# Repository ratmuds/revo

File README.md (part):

# revo

a cool robot arm

# Demo Video
# 

# What is it?

revo is a robot arm I made that is 6 DoF, and is equipped with 12 PCBs (5 unique designs), multiple cameras, many microcontrollers, and a lot of files

# Why?

I wanted to make a robot arm that punched above its weight. The price is pretty similar to smaller robot arms on Amazon that may not include cameras, which would need to be purchased separately. The way this is achieved is by using cheap servos, servos that are 100% NOT made for this purpose, and adding most of the functionality of a smart servo back by using a TON of PCBs. It was a lot of soldering. I just wanted to make something that had more features for less money :)

### Motors

Each motor has voltage, current, and a connector for a NTC thermistor for temperature monitoring. The MG996R servos each have a sensor PCB that plugs in and provides angle data via an AS5600 IC and another IC for a magnetic endstop since I had issues with physical endstops before. The MG996R needs a custom case to mount everything, which took me an incredible amount of time to get working due to super weird tolerances, especially the way I have it working requiring a separate 3D printed extension for the shaft to mount a magnet. The code also has to track this magnet super fast and track how many full revolutions it makes, and calculates the correct real angle from that. It's also running LADRC instead of basic sweep or PID, which has helped a little with jittering and general inaccuracies.

Each MG996R servo has two JST-VH connectors and two JST-1.25mm connectors. They daisy chain 6V and a RS-485 bus for reliable data transfer. The daisy chaining helps with the wiring, and the differential signals help with noise resistance and the distance. Each servo compares a checksum and magic byte that is received to verify data integrity before loading it into structs and using the data. They have multiple LEDs to provide information such as errors, calibration status, data corruption, invalid PCB ID, code alive status, etc.

### Mainboard

The mainboard has a RPi Pico for controlling, and a bunch of sensors for the DS5180 servo motors. The mainboard also has a two step power circuit that requires a logic signal from the Pico and the E-STOP to be depressed to allow the electricity to flow through. This is then routed to 3 separate buck modules that regulate the voltage. There is a 6V module for the MG996Rs, and two 7.4V modules for the DS5180s. There are also two smaller modules for 12V and 3.3V.

### Control

There are multiple ways to control the robot arm, such as manually controlling the values in the dashboard, dragging IK in the dashboard, or the coolest way, VR. You can see it in action in the demo video above :)

## Some images

### More images in the [`/PCB`](PCB/) folder!

# Looking back

There are a lot of not great things with this arm. The mainboard is incredibly hard to assemble. The screws like to fall out. There are cables everywhere despite me trying to clean it up a bit. And it's inaccurate. But that's because the motors I'm using are literally like $5 each. I would recommend better motors if you want to make a robot arm, but this project was just to see if I could do it and pushing my limits in all fields like programming, electronics, and CAD/mechanical design.

# "Installation"

## Please do not replicate this robot arm.
It is a proof of concept that is not ready for real world use. There are no instructions for building it because of that reason. It is a fragile piece of robotics and not meant for any sort of practical usage or replication! If you really want to, it's not that difficult though if you look through the CAD :)

There is a lot of different files.

 - `firmware/dashboard`: The dashboard for controlling and viewing telemetry data. Use `pnpm i` to install, `pnpm run dev` to run.
 - `firmware/mainboard-firmware`: Please use the Arduino IDE and compile for your RPi Pico board.
 - `firmware/pc-code`: Python backend for telemetry and cameras. Install dependencies with `pip install -r requirements.txt` (or use `uv run`). Run `python camera_server.py` to host the cameras (loads three) and `python main.py` to host the communication layer between the mainboard and the web dashboard.
 - `firmware/servo-firmware`: Please use PlatformIO in VSCode (or similar) and compile. You will need a UPDI programmer to upload the code to the MG996Rs containing ATtiny3216s. Note that the servos cannot output any serial so you will have to rely on LEDs if it's not communicating with the mainboard!

## VR

I used a Meta Quest 2 and used the Link app on my PC (GPU required) and you can go to `localhost:5173/VR` while hosting the dashboard to access the WebXR page.

## PCBs

The five PCB designs are in the `/PCB` folder. There are more images in that folder for reference. I ordered them and hand soldered them, which took a long time but I got faster as time went on.

## Bill of Materials (this is so so so long)

### Hardware & Components

Please don't actually build this project, but if you do ORDER SPARES!!!!!!

| Name | Type | Amount | Link | Notes |
| --- | --- | --- | --- | --- |
| 80KG High Torque Digital Servo (270°) | Servo Motor | 3 | [AliExpress](https://www.aliexpress.com/item/1005007314488392.html) | 1/5 scale waterproof metal gear servos for base, shoulder, and elbow joints |
| MG996R Metal Gear Digital Servo | Servo Motor | 4 | [AliExpress](https://www.aliexpress.com/item/1005008413371371.html) | 4.8V–6.0V high torque standard servos for wrist and gripper joints |
| 18T Round Disc Metal Servo Horn | Hardware | 2 | [AliExpress](https://www.aliexpress.us/item/3256807206931134.html?spm=a2g0o.productlist.main.9.741d8cce7npNM8&algo_pvid=76ea85b5-3475-48e7-a43c-c0fa06abfd4f&algo_exp_id=76ea85b5-3475-48e7-a43c-c0fa06abfd4f-8&pdp_ext_f=%7B%22order%22%3A%2287%22%2C%22eval%22%3A%221%22%2C%22fromPage%22%3A%22search%22%7D&pdp_npi=6%40dis%21USD%213.12%213.12%21%21%213.12%213.12%21%402101e75417906272356213761e0f7f%2112000040563545569%21sea%21US%212891746612%21X%211%210%21n_tag%3A-29919%3Bd%3A6dcb8e0a%3Bm03_new_user%3A-29895&curPageLogUid=LFs17y7q5TM3&utparam-url=scene%3Asearch%7Cquery_from%3A%7Cx_object_id%3A1005007393245886%7C_p_origin_prod%3A) | Round disc steering servo horn for 60KG/80KG/150KG servos |
| MG996R Metal Servo Horns (25T) | Hardware | 4 | [AliExpress](https://www.aliexpress.us/item/3256811964799543.html?spm=a2g0o.productlist.main.9.7dd94603On9EAE&algo_pvid=e16d6fb9-ca4b-46d7-a97f-2976e7b034ed&algo_exp_id=e16d6fb9-ca4b-46d7-a97f-2976e7b034ed-8&pdp_ext_f=%7B%22order%22%3A%2229%22%2C%22eval%22%3A%221%22%2C%22fromPage%22%3A%22search%22%7D&pdp_npi=6%40dis%21USD%213.45%213.45%21%21%2123.06%2123.06%21%402101d3fe17906272478427031e12ba%2112000057641054222%21sea%21US%212891746612%21X%211%210%21n_tag%3A-29919%3Bd%3A6dcb8e0a%3Bm03_new_user%3A-29895&curPageLogUid=k0UkhpWwbytt&utparam-url=scene%3Asearch%7Cquery_from%3A%7Cx_object_id%3A1005012151114295%7C_p_origin_prod%3A) | Metal steering servo horns for MG996R servos |
| 6806-2RS Deep Groove Ball Bearings | Bearing | 2 | [AliExpress](https://www.aliexpress.us/item/3256805896194394.html?spm=a2g0o.productlist.main.2.41e11384U8iG6y&algo_pvid=f9b76a2a-167c-4e4e-841b-79dc624c8d4b&algo_exp_id=f9b76a2a-167c-4e4e-841b-79dc624c8d4b-1&pdp_ext_f=%7B%22order%22%3A%22125%22%2C%22eval%22%3A%221%22%2C%22fromPage%22%3A%22search%22%7D&pdp_npi=6%40dis%21USD%219.04%219.04%21%21%2160.37%2160.37%21%402101c4ea17906272603893088e0f91%2112000058220110375%21sea%21US%212891746612%21X%211%210%21n_tag%3A-29919%3Bd%3A6dcb8e0a%3Bm03_new_user%3A-29895&curPageLogUid=POW02X4nniLX&utparam-url=scene%3Asearch%7Cquery_from%3A%7Cx_object_id%3A1005006082509146%7C_p_origin_prod%3A) | 30mm ID x 42mm OD x 7mm bore double sealed chrome steel bearings for joints |
| Radial Magnet for AS5600 | Magnet | 4 | [AliExpress](https://www.aliexpress.us/item/3256812696378533.html?spm=a2g0o.productlist.main.2.48406a91DkZk8e&algo_pvid=4a875b4f-6416-449f-8e05-ff96177a24f1&algo_exp_id=4a875b4f-6416-449f-8e05-ff96177a24f1-1&pdp_ext_f=%7B%22order%22%3A%2213%22%2C%22eval%22%3A%221%22%2C%22fromPage%22%3A%22search%22%7D&pdp_npi=6%40dis%21USD%216.36%213.18%21%21%2142.50%2121.25%21%402101de2517906272868341093e11d8%2112000059612191183%21sea%21US%212891746612%21X%211%210%21n_tag%3A-29919%3Bd%3A6dcb8e0a%3Bm03_new_user%3A-29895&curPageLogUid=ms3lq8WgvvyG&utparam-url=scene%3Asearch%7Cquery_from%3A%7Cx_object_id%3A1005012882693285%7C_p_origin_prod%3A) | Diametrically / radially magnetized disc magnets for AS5600 magnetic encoders |
| 6x2mm Neodymium Disc Magnets (N35) | Magnet | 1 pack | [AliExpress](https://www.aliexpress.us/item/3256812381175382.html?spm=a2g0o.productlist.main.3.6e12487dHqL9Ct&algo_pvid=693e3c62-3070-488b-8001-e15c0f3d7e28&algo_exp_id=693e3c62-3070-488b-8001-e15c0f3d7e28-2&pdp_ext_f=%7B%22order%22%3A%2253%22%2C%22eval%22%3A%221%22%2C%22fromPage%22%3A%22search%22%7D&pdp_npi=6%40dis%21USD%215.60%212.69%21%21%2137.41%2117.96%21%402101c4ea17906272969054365e0f91%2112000058717549322%21sea%21US%212891746612%21X%211%210%21n_tag%3A-29919%3Bd%3A6dcb8e0a%3Bm03_new_user%3A-29895&curPageLogUid=hxDDuVEMocB6&utparam-url=scene%3Asearch%7Cquery_from%3A%7Cx_object_id%3A1005012567490134%7C_p_origin_prod%3A) | Permanent NdFeB round magnets for latching/accessories |
| M2.5 Heat-Set Brass Threaded Inserts | Fastener | 100 pcs | [AliExpress](https://www.aliexpress.us/item/3256803590420762.html?spm=a2g0o.productlist.main.14.19a76574rk2ndf&aem_p4p_detail=202609281328263733255428752400003091825&algo_pvid=baa92169-4d62-48dd-aeb0-b23878ee4405&algo_exp_id=baa92169-4d62-48dd-aeb0-b23878ee4405-43&pdp_ext_f=%7B%22order%22%3A%22167%22%2C%22eval%22%3A%221%22%2C%22fromPage%22%3A%22search%22%7D&pdp_npi=6%40dis%21USD%2111.79%2111.79%21%21%2178.75%2178.75%21%402101e81117906273061306894e12c1%2112000032373736921%21sea%21US%212891746612%21X%211%210%21n_tag%3A-29919%3Bd%3A6dcb8e0a%3Bm03_new_user%3A-29895&curPageLogUid=q4oyedIYWKRR&utparam-url=scene%3Asearch%7Cquery_from%3A%7Cx_object_id%3A1005003776735514%7C_p_origin_prod%3A&search_p4p_id=202609281328263733255428752400003091825_17) | M2.5 x 3mm x 4mm knurled embed nuts for 3D printed components |
| M2.5 Screw Assortment | Fastener | 1 pack | [AliExpress](https://www.aliexpress.us/item/3256806640918365.html?spm=a2g0o.productlist.main.9.181c4f02NWcati&algo_pvid=20bfa238-2b80-45d9-8078-9c2e490b0b57&algo_exp_id=20bfa238-2b80-45d9-8078-9c2e490b0b57-8&pdp_ext_f=%7B%22order%22%3A%221542%22%2C%22eval%22%3A%221%22%2C%22fromPage%22%3A%22search%22%7D&pdp_npi=6%40dis%21USD%216.60%216.60%21%21%216.60%216.60%21%402101c4ea17906273345485918e0f91%2112000038430358098%21sea%21US%212891746612%21X%211%210%21n_tag%3A-29919%3Bd%3A6dcb8e0a%3Bm03_new_user%3A-29895&curPageLogUid=zy6gPLESrgR4&utparam-url=scene%3Asearch%7Cquery_from%3A%7Cx_object_id%3A1005006827233117%7C_p_origin_prod%3A) | Assorted lengths for robot arm structure and PCB mounting |
| M3 Low-Profile Socket Head Screws | Fastener | 1 pack | [AliExpress](https://www.aliexpress.us/item/3256811908204179.html?spm=a2g0o.productlist.main.1.6c701a36cwFl4T&algo_pvid=5edc6ef6-8dd0-471a-b58c-11b12b14439c&algo_exp_id=5edc6ef6-8dd0-471a-b58c-11b12b14439c-0&pdp_ext_f=%7B%22order%22%3A%22184%22%2C%22eval%22%3A%221%22%2C%22fromPage%22%3A%22search%22%7D&pdp_npi=6%40dis%21USD%214.73%213.12%21%21%2131.61%2120.86%21%402101e75417906273654458437e0f7f%2112000057505828552%21sea%21US%212891746612%21X%211%210%21n_tag%3A-29919%3Bd%3A6dcb8e0a%3Bm03_new_user%3A-29895&curPageLogUid=XCd8gqRaE6Fo&utparam-url=scene%3Asearch%7Cquery_from%3A%7Cx_object_id%3A1005012094518931%7C_p_origin_prod%3A) | 304 stainless steel Allen hex thin/short head cap bolts |
| 180W Dell Power Supply AC Adapter | Power Supply | 1 | [Amazon](https://a.co/d/06vQQfGW) | 19.5V 180W power brick for main system power |
| Dell 7.4x5.0mm to XT60 Adapter (XT-017) | Adapter | 1 | [Amazon](https://a.co/d/06vQQfGW) | Converts Dell power brick 7.4x5.0mm barrel jack to XT60 plug |
| 10A Step-Down Buck Converter Module | Buck Converter Module | 2 | [AliExpress](https://www.aliexpress.us/item/3256806146157850.html?spm=a2g0o.productlist.main.7.39251854tdn8R4&algo_pvid=99a51226-e349-4bcd-9ac8-cdfddf15871a&algo_exp_id=99a51226-e349-4bcd-9ac8-cdfddf15871a-6&pdp_ext_f=%7B%22order%22%3A%2279%22%2C%22eval%22%3A%221%22%2C%22fromPage%22%3A%22search%22%7D&pdp_npi=6%40dis%21USD%214.54%214.54%21%21%214.54%214.54%21%402101ca9517906273779526770e12b4%2112000036791314056%21sea%21US%212891746612%21X%211%210%21n_tag%3A-29919%3Bd%3A6dcb8e0a%3Bm03_new_user%3A-29895&curPageLogUid=Pok4rQpN3UOF&utparam-url=scene%3Asearch%7Cquery_from%3A%7Cx_object_id%3A1005006332472602%7C_p_origin_prod%3A) | 4-32V to 1.2-32V adjustable CV/CC step-down regulator for servo/system power |
| MP1584EN 3A Buck Converter Module | Buck Converter Module | 2 | [AliExpress](https://www.aliexpress.us/item/3256805684077964.html?spm=a2g0o.productlist.main.3.d7464cb3NAxnsx&algo_pvid=07f49b81-1bae-49f5-994e-3b5f6c2dd288&algo_exp_id=07f49b81-1bae-49f5-994e-3b5f6c2dd288-2&pdp_ext_f=%7B%22order%22%3A%222710%22%2C%22eval%22%3A%221%22%2C%22fromPage%22%3A%22search%22%7D&pdp_npi=6%40dis%21USD%212.33%212.33%21%21%212.33%212.33%21%402101ca9517906273914747154e12b4%2112000034645748479%21sea%21US%212891746612%21X%211%210%21n_tag%3A-29919%3Bd%3A6dcb8e0a%3Bm03_new_user%3A-29895&curPageLogUid=iltiNSEJm1Hn&utparam-url=scene%3Asearch%7Cquery_from%3A%7Cx_object_id%3A1005005870392716%7C_p_origin_prod%3A) | Ultra-compact 3A adjustable DC-DC step-down power module (Mini360 style) |
| Red Mushroom Emergency Stop Switch | Switch | 1 | [AliExpress](https://www.aliexpress.us/item/3256803936809498.html?spm=a2g0o.productlist.main.5.2ccc4cd1hgyLus&algo_pvid=0b5cd7e2-f8f4-44fe-b74f-acdf3ea81a96&algo_exp_id=0b5cd7e2-f8f4-44fe-b74f-acdf3ea81a96-4&pdp_ext_f=%7B%22order%22%3A%22161%22%2C%22eval%22%3A%221%22%2C%22fromPage%22%3A%22search%22%7D&pdp_npi=6%40dis%21USD%212.52%212.52%21%21%212.52%212.52%21%402101e81117906274017701232e13a8%2112000028111320834%21sea%21US%212891746612%21X%211%210%21n_tag%3A-29919%3Bd%3A6dcb8e0a%3Bm03_new_user%3A-29895&curPageLogUid=y1Tc0yCfzeM6&utparam-url=scene%3Asearch%7Cquery_from%3A%7Cx_object_id%3A1005004123124250%7C_p_origin_prod%3A) | 1NO 1NC DPST latching push-button E-STOP switch (660V 10A, plugs into J17) |
| AR0144 720P 60fps Global Shutter Camera | Camera | 1 | [Amazon](https://a.co/d/0btbj34H) | High-speed 170° fisheye USB camera module for tracking and vision |
| OV9726 1MP USB Camera Module | Camera | 4 | [AliExpress](https://www.aliexpress.us/item/3256811684370860.html) | 720P CMOS 50° FOV USB cameras (used in camera_server.py) |
| 3010 Cooling Fan (12V) | Fan | 1 | [AliExpress](https://www.aliexpress.us/item/3256803185681643.html?spm=a2g0o.productlist.main.1.267368940Db7Nv&algo_pvid=f4bcd9d5-27c3-4918-8243-0b9482f00a25&algo_exp_id=f4bcd9d5-27c3-4918-8243-0b9482f00a25-0&pdp_ext_f=%7B%22order%22%3A%226020%22%2C%22eval%22%3A%221%22%2C%22fromPage%22%3A%22search%22%7D&pdp_npi=6%40dis%21USD%211.92%211.92%21%21%211.92%211.92%21%402101e7a317906274159744877e10c3%2112000025471466562%21sea%21US%212891746612%21X%211%210%21n_tag%3A-29919%3Bd%3A6dcb8e0a%3Bm03_new_user%3A-29895&curPageLogUid=3dQF4QAgCQwg&utparam-url=scene%3Asearch%7Cquery_from%3A%7Cx_object_id%3A1005003371996395%7C_p_origin_prod%3A) | 30x30x10mm 2-pin 12V DC cooling fan (connects to FAN PWR J24/J23) |
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
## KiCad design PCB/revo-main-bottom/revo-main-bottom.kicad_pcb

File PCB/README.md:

# PCBs

These are all the PCBs I designed for the revo robot arm. Ordered through JLCPCB. BOM is in `BOM.csv` and the root `README.md`.

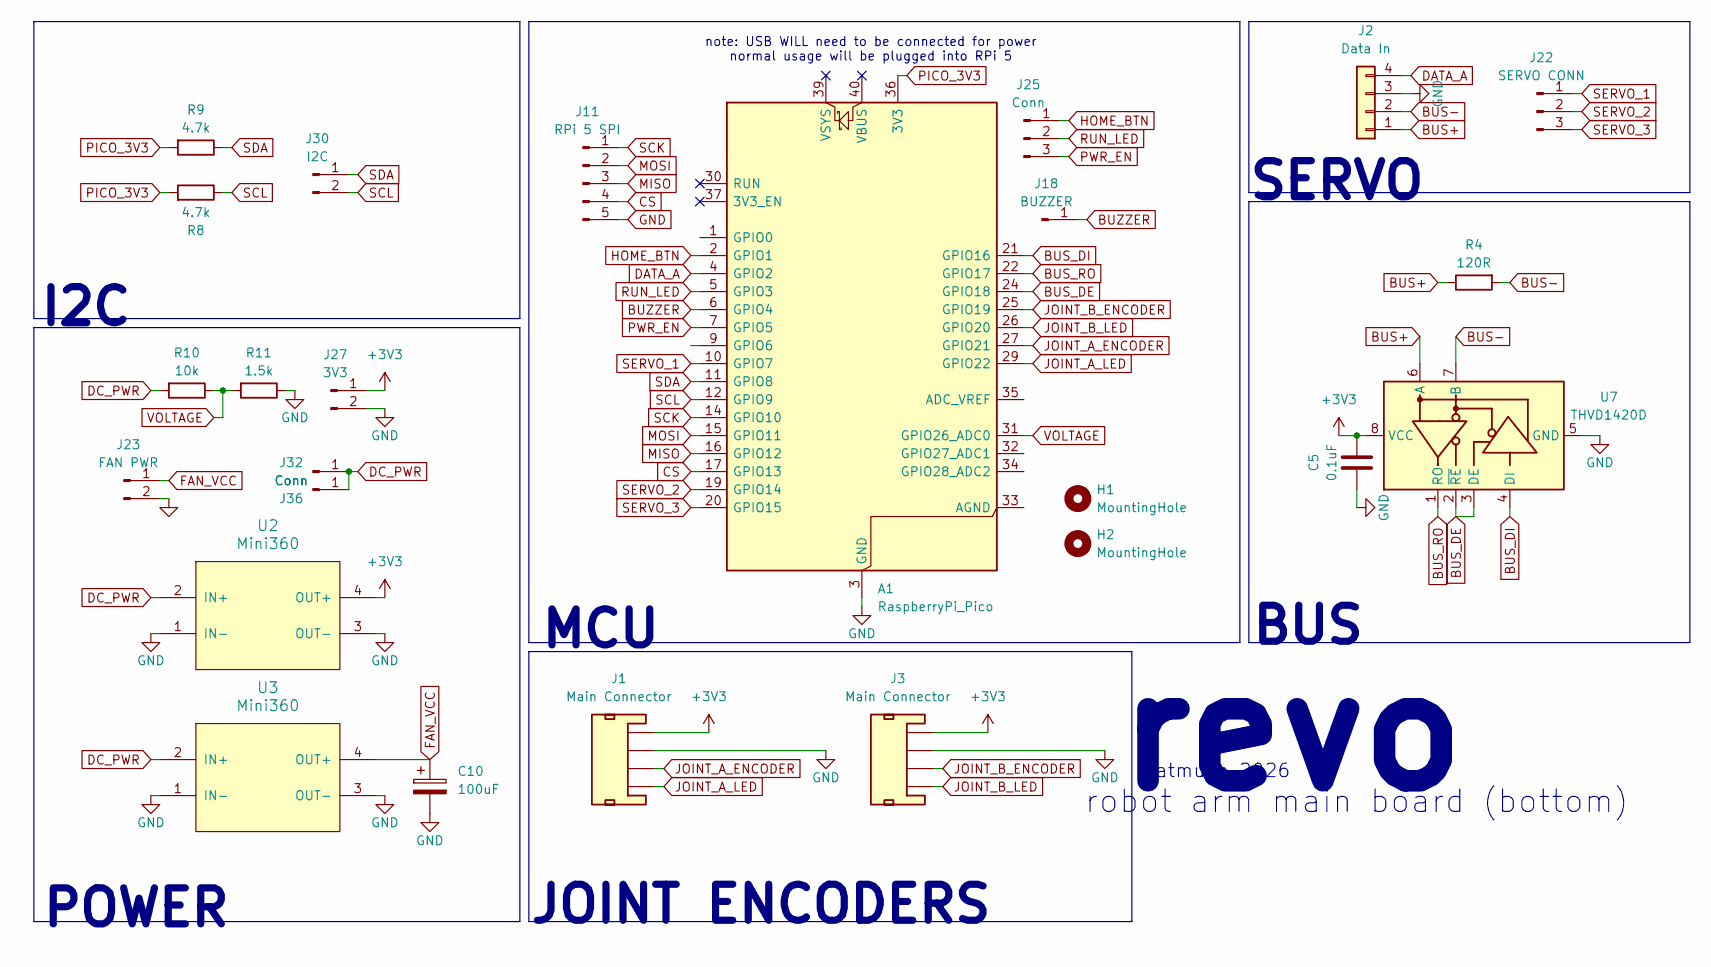
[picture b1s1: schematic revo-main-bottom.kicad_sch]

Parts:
A1: RaspberryPi_Pico; RaspberryPi_Pico_Common_Unspecified
C5: 0.1uF; C_0805_2012Metric_Pad1.18x1.45mm_HandSolder
C10: 100uF; CP_Radial_D6.3mm_P2.50mm; MPN 732-8707-1-ND
H1, H2: MountingHole; MountingHole_3.2mm_M3
J1, J3: Main Connector; JST_1x04_P2.0mm_Vertical_PTH
J2: Data In; JST_1x04_P1.25mm_Locking_Horizontal_SMD
J11: RPi 5 SPI; PinHeader_1x05_P2.54mm_Vertical
J18: BUZZER; PinHeader_1x01_P2.54mm_Vertical
J22: SERVO CONN; PinHeader_1x03_P2.54mm_Vertical
J23: FAN PWR; PinHeader_1x02_P2.54mm_Vertical
J25: Conn; PinHeader_1x03_P2.54mm_Vertical
J27: 3V3; PinHeader_1x02_P2.54mm_Vertical
J30: I2C; PinHeader_1x02_P2.54mm_Vertical
J32, J36: Conn; PinHeader_1x01_P2.54mm_Vertical
R4: 120R; R_0805_2012Metric_Pad1.20x1.40mm_HandSolder
R8, R9: 4.7k; R_0805_2012Metric_Pad1.20x1.40mm_HandSolder
R10: 10k; R_0805_2012Metric_Pad1.20x1.40mm_HandSolder
R11: 1.5k; R_0805_2012Metric_Pad1.20x1.40mm_HandSolder
U2, U3: Mini360; Mini360_step-down
U7: THVD1420D; SOIC-8_3.9x4.9mm_P1.27mm

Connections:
+3V3: C5.2, J1.4, J3.4, J27.1, U2.4 (OUT+), U7.8 (VCC)
BUS+: J2.1, R4.1, U7.6 (A)
BUS-: J2.2, R4.2, U7.7 (B)
BUS_DE: A1.24 (GPIO18), U7.2 (~RE), U7.3 (DE)
BUS_DI: A1.21 (GPIO16), U7.4 (DI)
BUS_RO: A1.22 (GPIO17), U7.1 (RO)
BUZZER: A1.6 (GPIO4), J18.1 (Pin_1_1)
CS: A1.17 (GPIO13), J11.4
DATA_A: A1.4 (GPIO2), J2.4
DC_PWR: J32.1 (Pin_1_1), J36.1 (Pin_1_1), R10.2, U2.2 (IN+), U3.2 (IN+)
FAN_VCC: C10.1, J23.1, U3.4 (OUT+)
GND: A1.3 (GND), A1.8 (GND), A1.13 (GND), A1.18 (GND), A1.23 (GND), A1.28 (GND), A1.38 (GND), C5.1, C10.2, J1.3, J2.3, J3.3, J11.5, J23.2, J27.2, R11.1, U2.1 (IN-), U2.3 (OUT-), U3.1 (IN-), U3.3 (OUT-), U7.5 (GND)
HOME_BTN: A1.2 (GPIO1), J25.1
JOINT_A_ENCODER: A1.27 (GPIO21), J1.2
JOINT_A_LED: A1.29 (GPIO22), J1.1
JOINT_B_ENCODER: A1.25 (GPIO19), J3.2
JOINT_B_LED: A1.26 (GPIO20), J3.1
MISO: A1.16 (GPIO12), J11.3
MOSI: A1.15 (GPIO11), J11.2
PICO_3V3: A1.36 (3V3), R8.2, R9.2
PWR_EN: A1.7 (GPIO5), J25.3
RUN_LED: A1.5 (GPIO3), J25.2
SCK: A1.14 (GPIO10), J11.1
SCL: A1.12 (GPIO9), J30.2, R8.1
SDA: A1.11 (GPIO8), J30.1, R9.1
SERVO_1: A1.10 (GPIO7), J22.1
SERVO_2: A1.19 (GPIO14), J22.2
SERVO_3: A1.20 (GPIO15), J22.3
VOLTAGE: A1.31 (GPIO26_ADC0), R10.1, R11.2

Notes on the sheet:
I2C
POWER
BUS
SERVO
note: USB WILL need to be connected for power normal usage will be plugged into RPi 5
robot arm main board (bottom)
revo
JOINT ENCODERS
ratmuds 2026
MCU

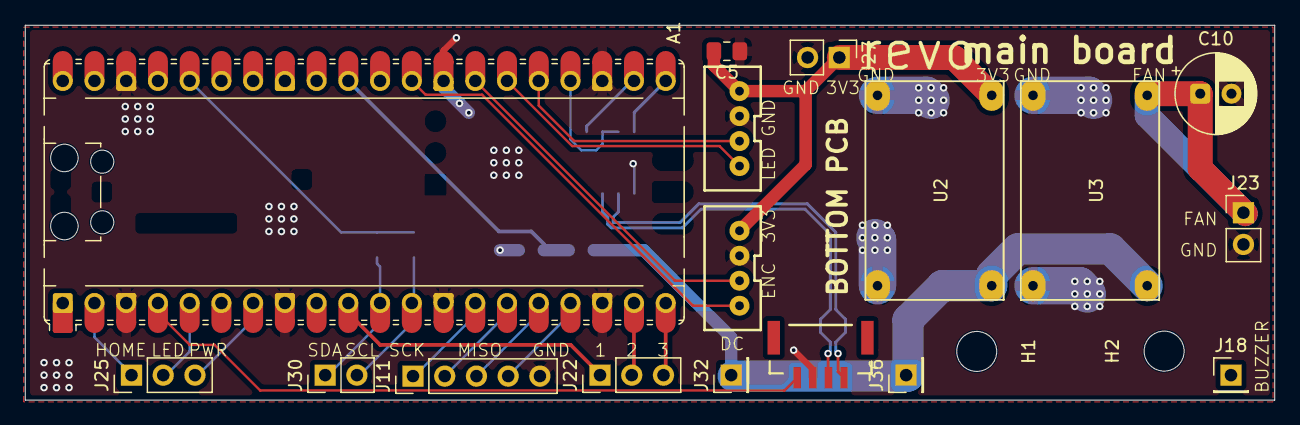
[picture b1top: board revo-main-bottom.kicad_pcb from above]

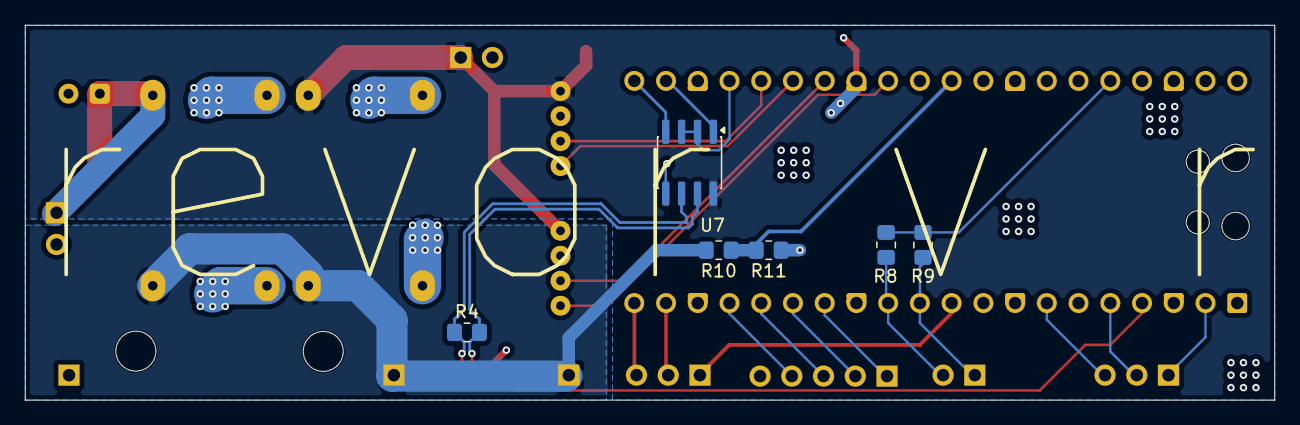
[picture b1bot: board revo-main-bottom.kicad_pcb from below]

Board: 4 copper layers, 100.0 x 30.0 mm, 25 parts (6 on the bottom side), 29 nets.

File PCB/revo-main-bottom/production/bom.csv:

Designator,Footprint,Quantity,Value,LCSC Part #
A1,RaspberryPi_Pico_Common_Unspecified,1,RaspberryPi_Pico,
C10,CP_Radial_D6.3mm_P2.50mm,1,100uF,732-8707-1-ND
C5,0805,1,0.1uF,
"J1, J3",JST_1x04_P2.0mm_Vertical_PTH,2,Main Connector,
J11,PinHeader_1x05_P2.54mm_Vertical,1,RPi 5 SPI,
J18,PinHeader_1x01_P2.54mm_Vertical,1,BUZZER,
J2,JST_1x04_P1.25mm_Locking_Horizontal_SMD,1,Data In,
J22,PinHeader_1x03_P2.54mm_Vertical,1,SERVO CONN,
J23,PinHeader_1x02_P2.54mm_Vertical,1,FAN PWR,
J25,PinHeader_1x03_P2.54mm_Vertical,1,Conn,
J27,PinHeader_1x02_P2.54mm_Vertical,1,3V3,
J30,PinHeader_1x02_P2.54mm_Vertical,1,I2C,
"J32, J36",PinHeader_1x01_P2.54mm_Vertical,2,Conn,
R10,0805,1,10k,
R11,0805,1,1.5k,
R4,0805,1,120R,
"R8, R9",0805,2,4.7k,
"U2, U3",Mini360_step-down,2,Mini360,
U7,SOIC-8_3.9x4.9mm_P1.27mm,1,THVD1420D,

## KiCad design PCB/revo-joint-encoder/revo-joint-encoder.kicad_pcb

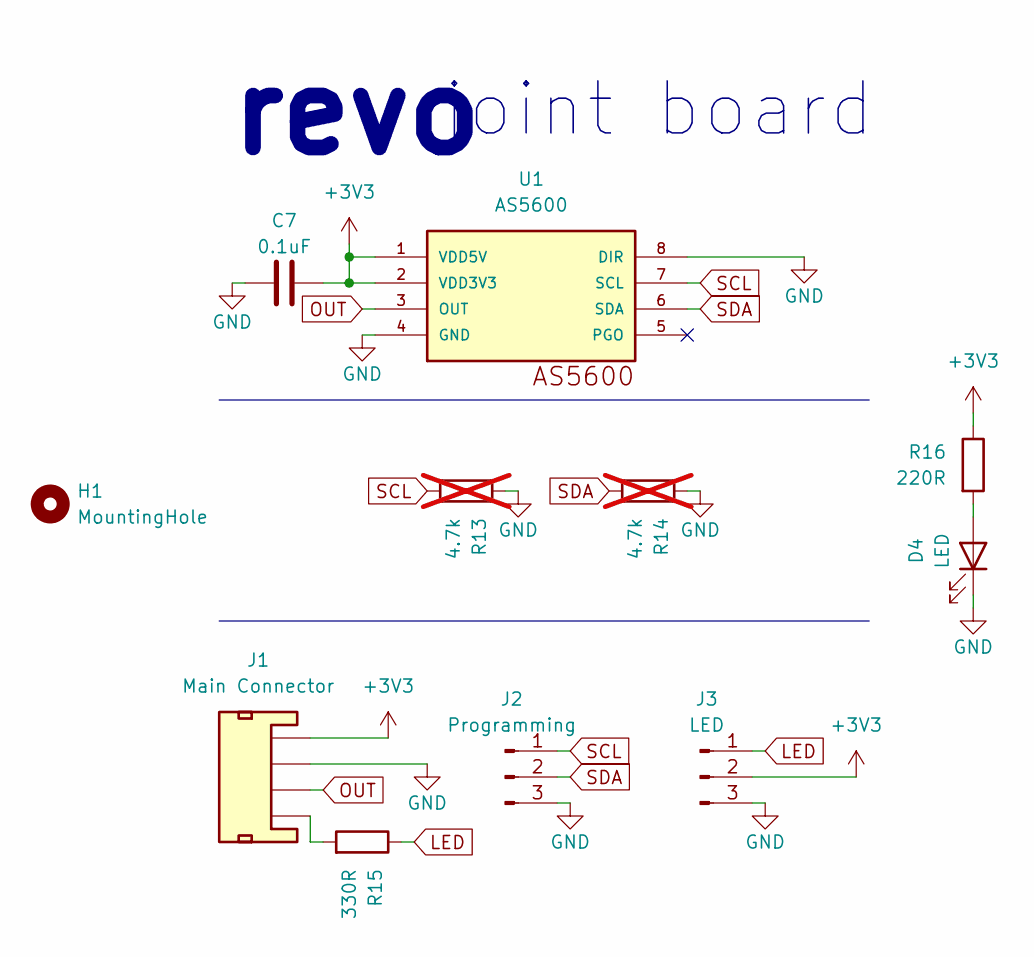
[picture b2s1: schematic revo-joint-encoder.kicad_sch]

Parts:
C7: 0.1uF; C_0805_2012Metric_Pad1.18x1.45mm_HandSolder
D4: LED; D_0805_2012Metric_Pad1.15x1.40mm_HandSolder
H1: MountingHole; MountingHole_3.2mm_M3
J1: Main Connector; JST_1x04_P2.0mm_Horizontal_PTH
J2: Programming; PinSocket_1x03_P2.54mm_Vertical
J3: LED; PinSocket_1x03_P2.54mm_Vertical
R13, R14: 4.7k; R_0805_2012Metric_Pad1.20x1.40mm_HandSolder; not fitted
R15: 330R; R_0805_2012Metric_Pad1.20x1.40mm_HandSolder
R16: 220R; R_0805_2012Metric_Pad1.20x1.40mm_HandSolder
U1: AS5600; SOIC8

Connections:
+3V3: C7.2, J1.4, J3.2, R16.1, U1.1 (VDD5V), U1.2 (VDD3V3)
GND: C7.1, D4.1 (K), J1.3, J2.3, J3.3, R13.1, R14.1, U1.4 (GND), U1.8 (DIR)
LED: J3.1, R15.1
unnamed: D4.2 (A), R16.2
unnamed: J1.1, R15.2
OUT: J1.2, U1.3 (OUT)
SCL: J2.1, R13.2, U1.7 (SCL)
SDA: J2.2, R14.2, U1.6 (SDA)

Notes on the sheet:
revo
joint board

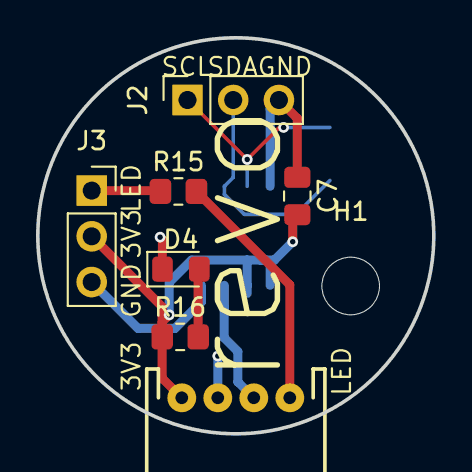
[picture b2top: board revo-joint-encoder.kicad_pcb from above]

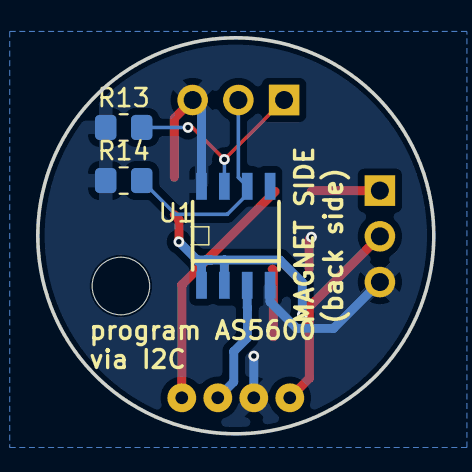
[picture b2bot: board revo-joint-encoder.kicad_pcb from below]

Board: 2 copper layers, 22.0 x 22.0 mm, 11 parts (3 on the bottom side), 8 nets.

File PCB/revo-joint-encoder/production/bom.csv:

Designator,Footprint,Quantity,Value,LCSC Part #
C7,0805,1,0.1uF,
D4,0805,1,LED,
J1,JST_1x04_P2.0mm_Horizontal_PTH,1,Main Connector,
J2,PinSocket_1x03_P2.54mm_Vertical,1,Programming,
J3,PinSocket_1x03_P2.54mm_Vertical,1,LED,
"R13, R14",0805,2,4.7k,
R15,0805,1,330R,
R16,0805,1,220R,
U1,SOIC8,1,AS5600,

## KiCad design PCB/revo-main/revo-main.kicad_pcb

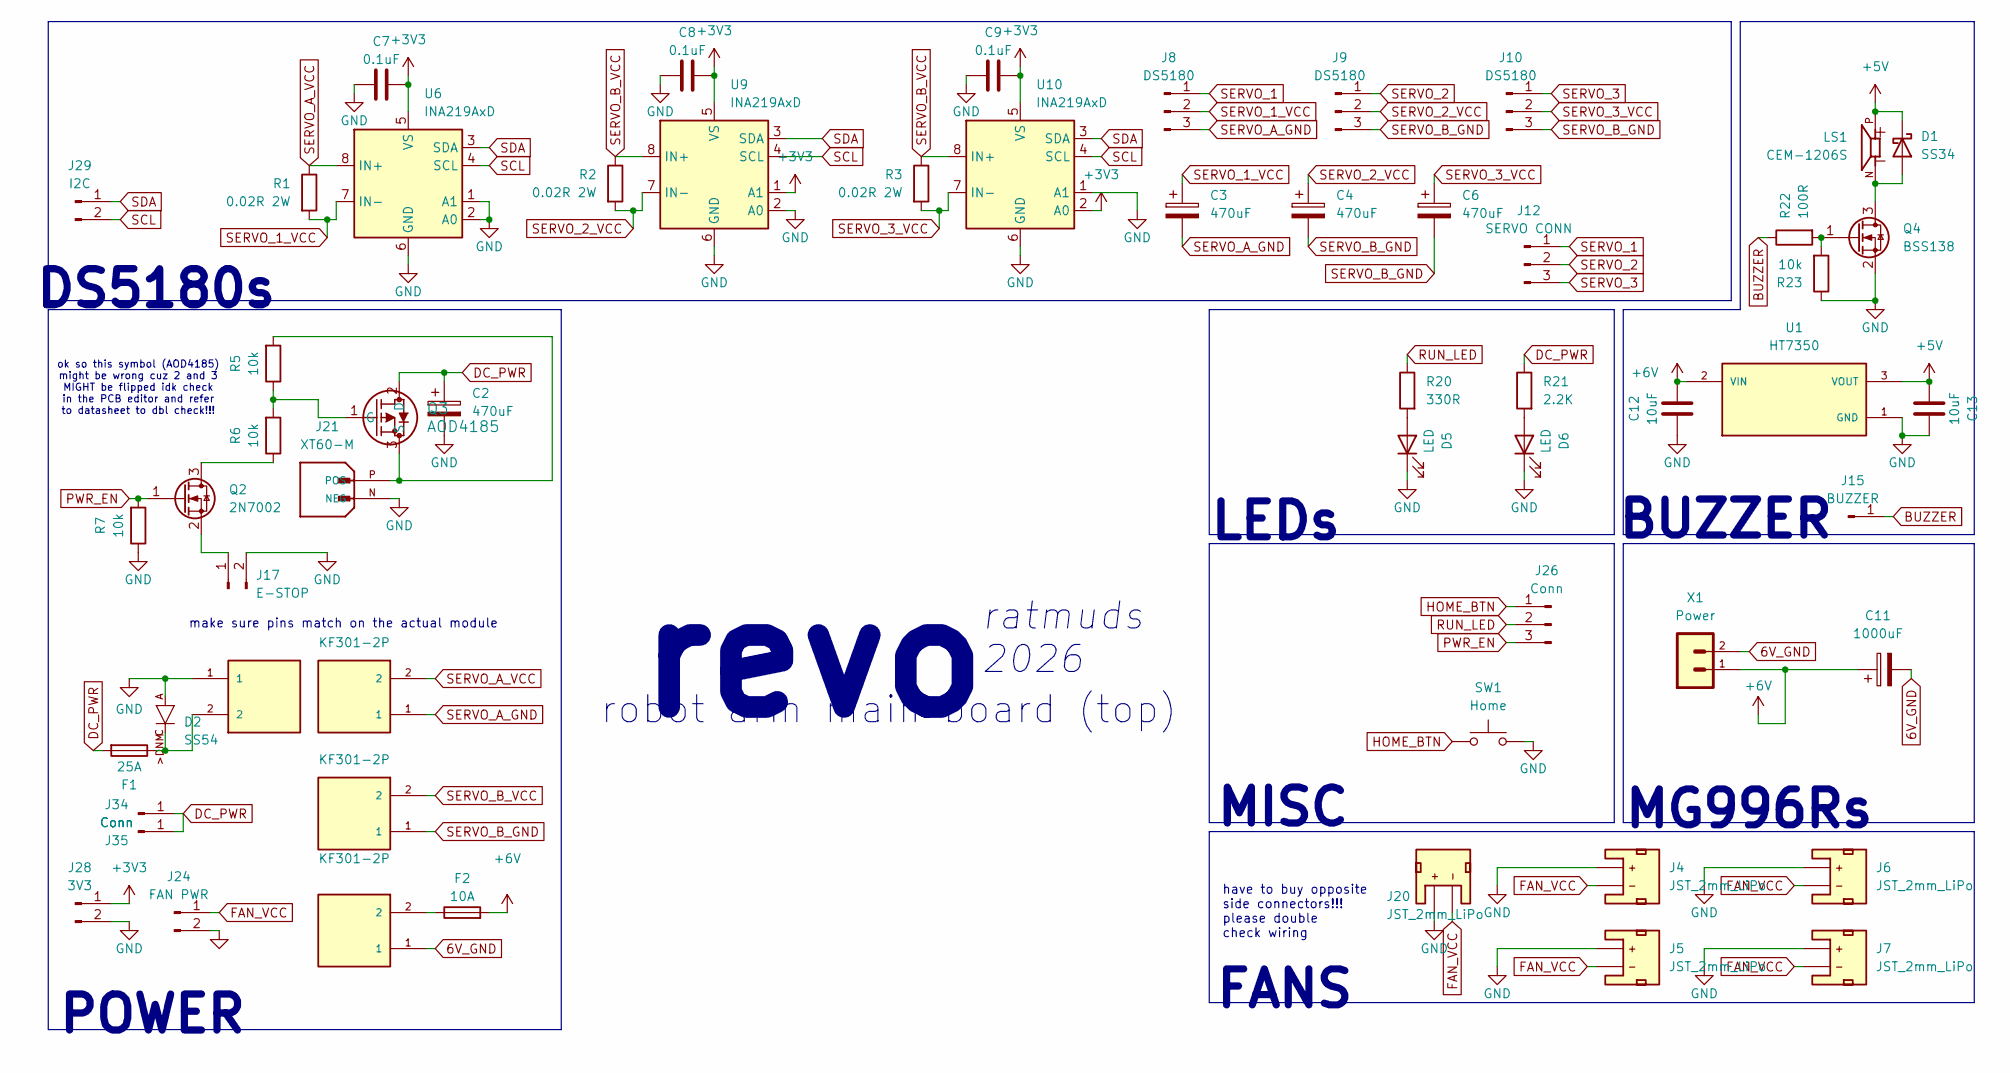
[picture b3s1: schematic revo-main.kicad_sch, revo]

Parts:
C2: 470uF; CP_Radial_D10.0mm_P5.00mm; MPN 35ZLH470MEFCT810X16
C3, C4, C6: 470uF; CP_Radial_D10.0mm_P5.00mm; MPN 25ZLH470MEFC10X12.5
C7, C8, C9: 0.1uF; C_0805_2012Metric_Pad1.18x1.45mm_HandSolder
C11: 1000uF; CP_Radial_D10.0mm_P5.00mm; MPN 16ZLH1000MEFC10X16
C12, C13: 10uF; C_0805_2012Metric_Pad1.18x1.45mm_HandSolder
D1: SS34; D_SMA
D2: SS54; DO-214AC; MPN SS54
D5, D6: LED; D_0805_2012Metric_Pad1.15x1.40mm_HandSolder
F1: 25A; Fuse_1808
F2: 10A; Fuse_1808
J4, J5, J6, J7, J20: JST_2mm_LiPo; JST_PH_B2B-PH-K_1x02_P2.00mm_Vertical
J8, J9, J10: DS5180; PinHeader_1x03_P2.54mm_Vertical
J12: SERVO CONN; PinHeader_1x03_P2.54mm_Vertical
J13: KF301-2P; KF7.62_2P; PARTREV NA
J14, J16, J19: KF301-2P; HANDSON_KF301-2P; PARTREV NA
J15: BUZZER; PinHeader_1x01_P2.54mm_Vertical
J17: E-STOP; PinHeader_1x02_P2.54mm_Vertical
J21: XT60-M; AMASS_XT60-M; PARTREV V1.2
J24: FAN PWR; PinHeader_1x02_P2.54mm_Vertical
J26: Conn; PinHeader_1x03_P2.54mm_Vertical
J28: 3V3; PinHeader_1x02_P2.54mm_Vertical
J29: I2C; PinHeader_1x02_P2.54mm_Vertical
J34, J35: Conn; PinHeader_1x01_P2.54mm_Vertical
LS1: CEM-1206S; CUI_CEM-1206S
Q2: 2N7002; SOT-23
Q3: AOD4185; TO-252-2
Q4: BSS138; SOT-23
R1, R2, R3: 0.02R 2W; R_2512_6332Metric_Pad1.40x3.35mm_HandSolder; MPN CRA2512-FZ-R020ELF
R5, R6, R7, R23: 10k; R_0805_2012Metric_Pad1.20x1.40mm_HandSolder
R20: 330R; R_0805_2012Metric_Pad1.20x1.40mm_HandSolder
R21: 2.2K; R_Axial_DIN0207_L6.3mm_D2.5mm_P10.16mm_Horizontal
R22: 100R; R_0805_2012Metric_Pad1.20x1.40mm_HandSolder
SW1: Home; SW_Tactile_SPST_NO_Straight_CK_PTS636Sx25SMTRLFS
U1: HT7350; IC_HT7333; PARTREV 1.80
U6, U9, U10: INA219AxD; SOIC-8_3.9x4.9mm_P1.27mm
X1: Power; B2PS-VH

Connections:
6V_GND: C11.2, J16.1, X1.2
+3V3: C7.2, C8.2, C9.2, J28.1, U6.5 (VS), U9.1 (A1), U9.5 (VS), U10.2 (A0), U10.5 (VS)
+5V: C13.2, D1.1 (K), LS1.P, U1.3 (VOUT)
+6V: C11.1, C12.2, F2.2, U1.2 (VIN), X1.1
BUZZER: J15.1 (Pin_1_1), R22.1
DC_PWR: C2.1, F1.2, J34.1 (Pin_1_1), J35.1 (Pin_1_1), Q3.2 (D), R21.1
FAN_VCC: J4.1 (-), J5.1 (-), J6.1 (-), J7.1 (-), J20.1 (-), J24.1
GND: C2.2, C7.1, C8.1, C9.1, C12.1, C13.1, D2.A, D5.1 (K), D6.1 (K), J4.2 (+), J5.2 (+), J6.2 (+), J7.2 (+), J13.1, J17.2, J20.2 (+), J21.N (NEG), J24.2, J28.2, Q4.2 (S), R7.1, R23.1, SW1.2, U1.1 (GND), U6.1 (A1), U6.2 (A0), U6.6 (GND), U9.2 (A0), U9.6 (GND), U10.1 (A1), U10.6 (GND)
HOME_BTN: J26.1, SW1.1
unnamed: D1.2 (A), LS1.N, Q4.3 (D)
unnamed: D2.C, F1.1, J13.2
unnamed: D5.2 (A), R20.2
unnamed: D6.2 (A), R21.2
unnamed: F2.1, J16.2
unnamed: J17.1, Q2.2 (S)
unnamed: J21.P (POS), Q3.3 (S), R5.2
unnamed: Q2.3 (D), R6.1
unnamed: Q3.1 (G), R5.1, R6.2
unnamed: Q4.1 (G), R22.2, R23.2
PWR_EN: J26.3, Q2.1 (G), R7.2
RUN_LED: J26.2, R20.1
SCL: J29.2, U6.4 (SCL), U9.4 (SCL), U10.4 (SCL)
SDA: J29.1, U6.3 (SDA), U9.3 (SDA), U10.3 (SDA)
SERVO_1: J8.1, J12.1
SERVO_1_VCC: C3.1, J8.2, R1.2, U6.7 (IN-)
SERVO_2: J9.1, J12.2
SERVO_2_VCC: C4.1, J9.2, R2.2, U9.7 (IN-)
SERVO_3: J10.1, J12.3
SERVO_3_VCC: C6.1, J10.2, R3.2, U10.7 (IN-)
SERVO_A_GND: C3.2, J8.3, J14.1
SERVO_A_VCC: J14.2, R1.1, U6.8 (IN+)
SERVO_B_GND: C4.2, C6.2, J9.3, J10.3, J19.1
SERVO_B_VCC: J19.2, R2.1, R3.1, U9.8 (IN+), U10.8 (IN+)

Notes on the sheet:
MG996Rs
BUZZER
make sure pins match on the actual module
MISC
FANS
robot arm main board (top)
ratmuds 2026
POWER
revo
DS5180s
ok so this symbol (AOD4185) might be wrong cuz 2 and 3 MIGHT be flipped idk check in the PCB editor and refer to datasheet to dbl check!!!
have to buy opposite side connectors!!! please double check wiring
LEDs

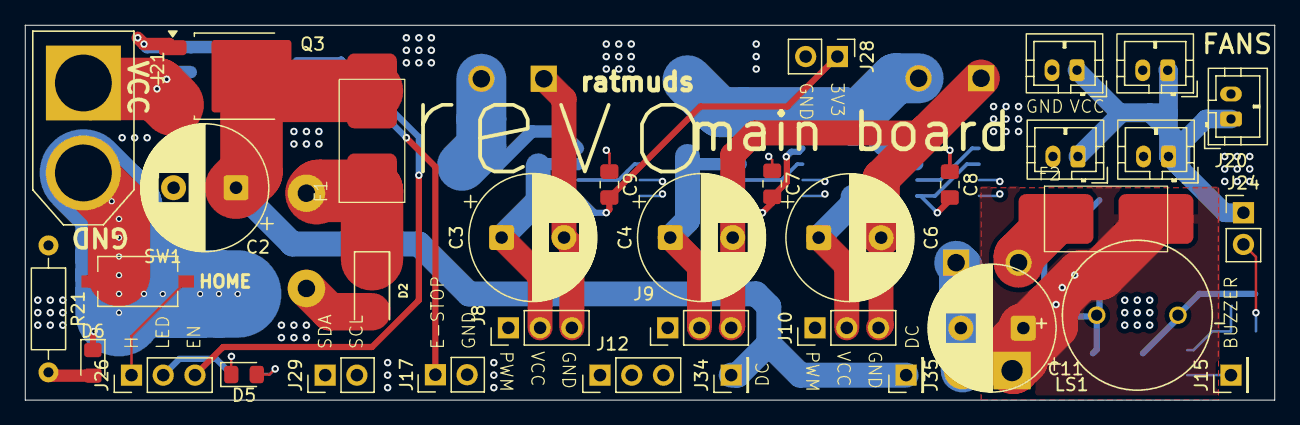
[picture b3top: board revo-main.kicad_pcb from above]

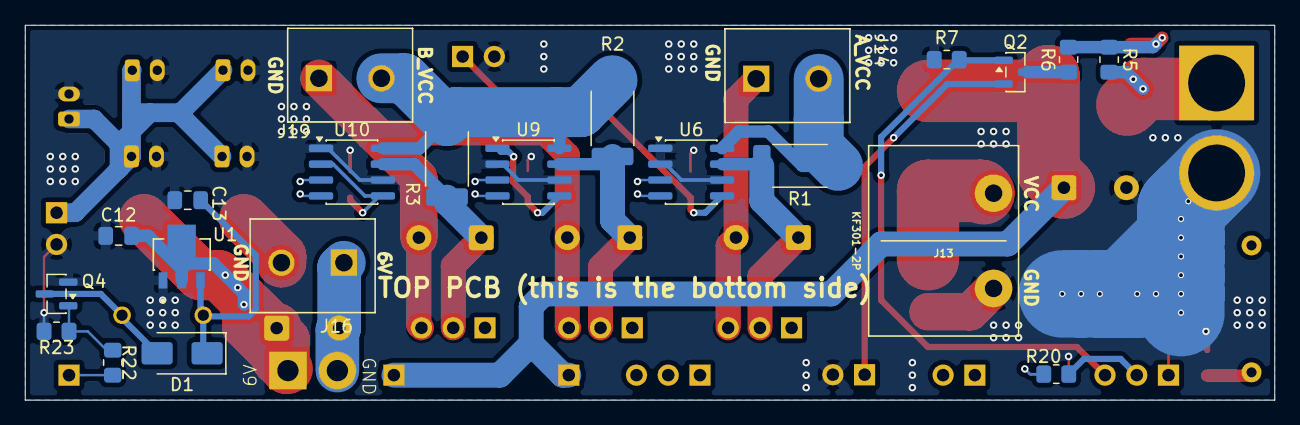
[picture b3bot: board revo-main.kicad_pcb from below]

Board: 4 copper layers, 100.0 x 30.0 mm, 58 parts (23 on the bottom side), 33 nets.

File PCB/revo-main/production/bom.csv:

Designator,Footprint,Quantity,Value,LCSC Part #
C11,CP_Radial_D10.0mm_P5.00mm,1,1000uF,16ZLH1000MEFC10X16
"C12, C13",0805,2,10uF,
C2,CP_Radial_D10.0mm_P5.00mm,1,470uF,35ZLH470MEFCT810X16
"C3, C4, C6",CP_Radial_D10.0mm_P5.00mm,3,470uF,25ZLH470MEFC10X12.5
"C7, C8, C9",0805,3,0.1uF,
D1,D_SMA,1,SS34,
D2,DO-214AC,1,SS54,SS54
"D5, D6",0805,2,LED,
F1,Fuse_1808,1,25A,
F2,Fuse_1808,1,10A,
"J10, J8, J9",PinHeader_1x03_P2.54mm_Vertical,3,DS5180,
J12,PinHeader_1x03_P2.54mm_Vertical,1,SERVO CONN,
J13,KF7.62_2P,1,KF301-2P,
"J14, J16, J19",HANDSON_KF301-2P,3,KF301-2P,
J15,PinHeader_1x01_P2.54mm_Vertical,1,BUZZER,
J17,PinHeader_1x02_P2.54mm_Vertical,1,E-STOP,
"J20, J4, J5, J6, J7",JST_PH_B2B-PH-K_1x02_P2.00mm_Vertical,5,JST_2mm_LiPo,
J21,AMASS_XT60-M,1,XT60-M,
J24,PinHeader_1x02_P2.54mm_Vertical,1,FAN PWR,
J26,PinHeader_1x03_P2.54mm_Vertical,1,Conn,
J28,PinHeader_1x02_P2.54mm_Vertical,1,3V3,
J29,PinHeader_1x02_P2.54mm_Vertical,1,I2C,
"J34, J35",PinHeader_1x01_P2.54mm_Vertical,2,Conn,
LS1,CUI_CEM-1206S,1,CEM-1206S,
Q2,SOT-23,1,2N7002,
Q3,TO-252-2,1,AOD4185,
Q4,SOT-23,1,BSS138,
"R1, R2, R3",2512,3,0.02R 2W,CRA2512-FZ-R020ELF
R20,0805,1,330R,
R21,R_Axial_DIN0207_L6.3mm_D2.5mm_P10.16mm_Horizontal,1,2.2K,
R22,0805,1,100R,
"R23, R5, R6, R7",0805,4,10k,
SW1,SW_Tactile_SPST_NO_Straight_CK_PTS636Sx25SMTRLFS,1,Home,
U1,IC_HT7333,1,HT7350,
"U10, U6, U9",SOIC-8_3.9x4.9mm_P1.27mm,3,INA219AxD,
X1,B2PS-VH,1,Power,

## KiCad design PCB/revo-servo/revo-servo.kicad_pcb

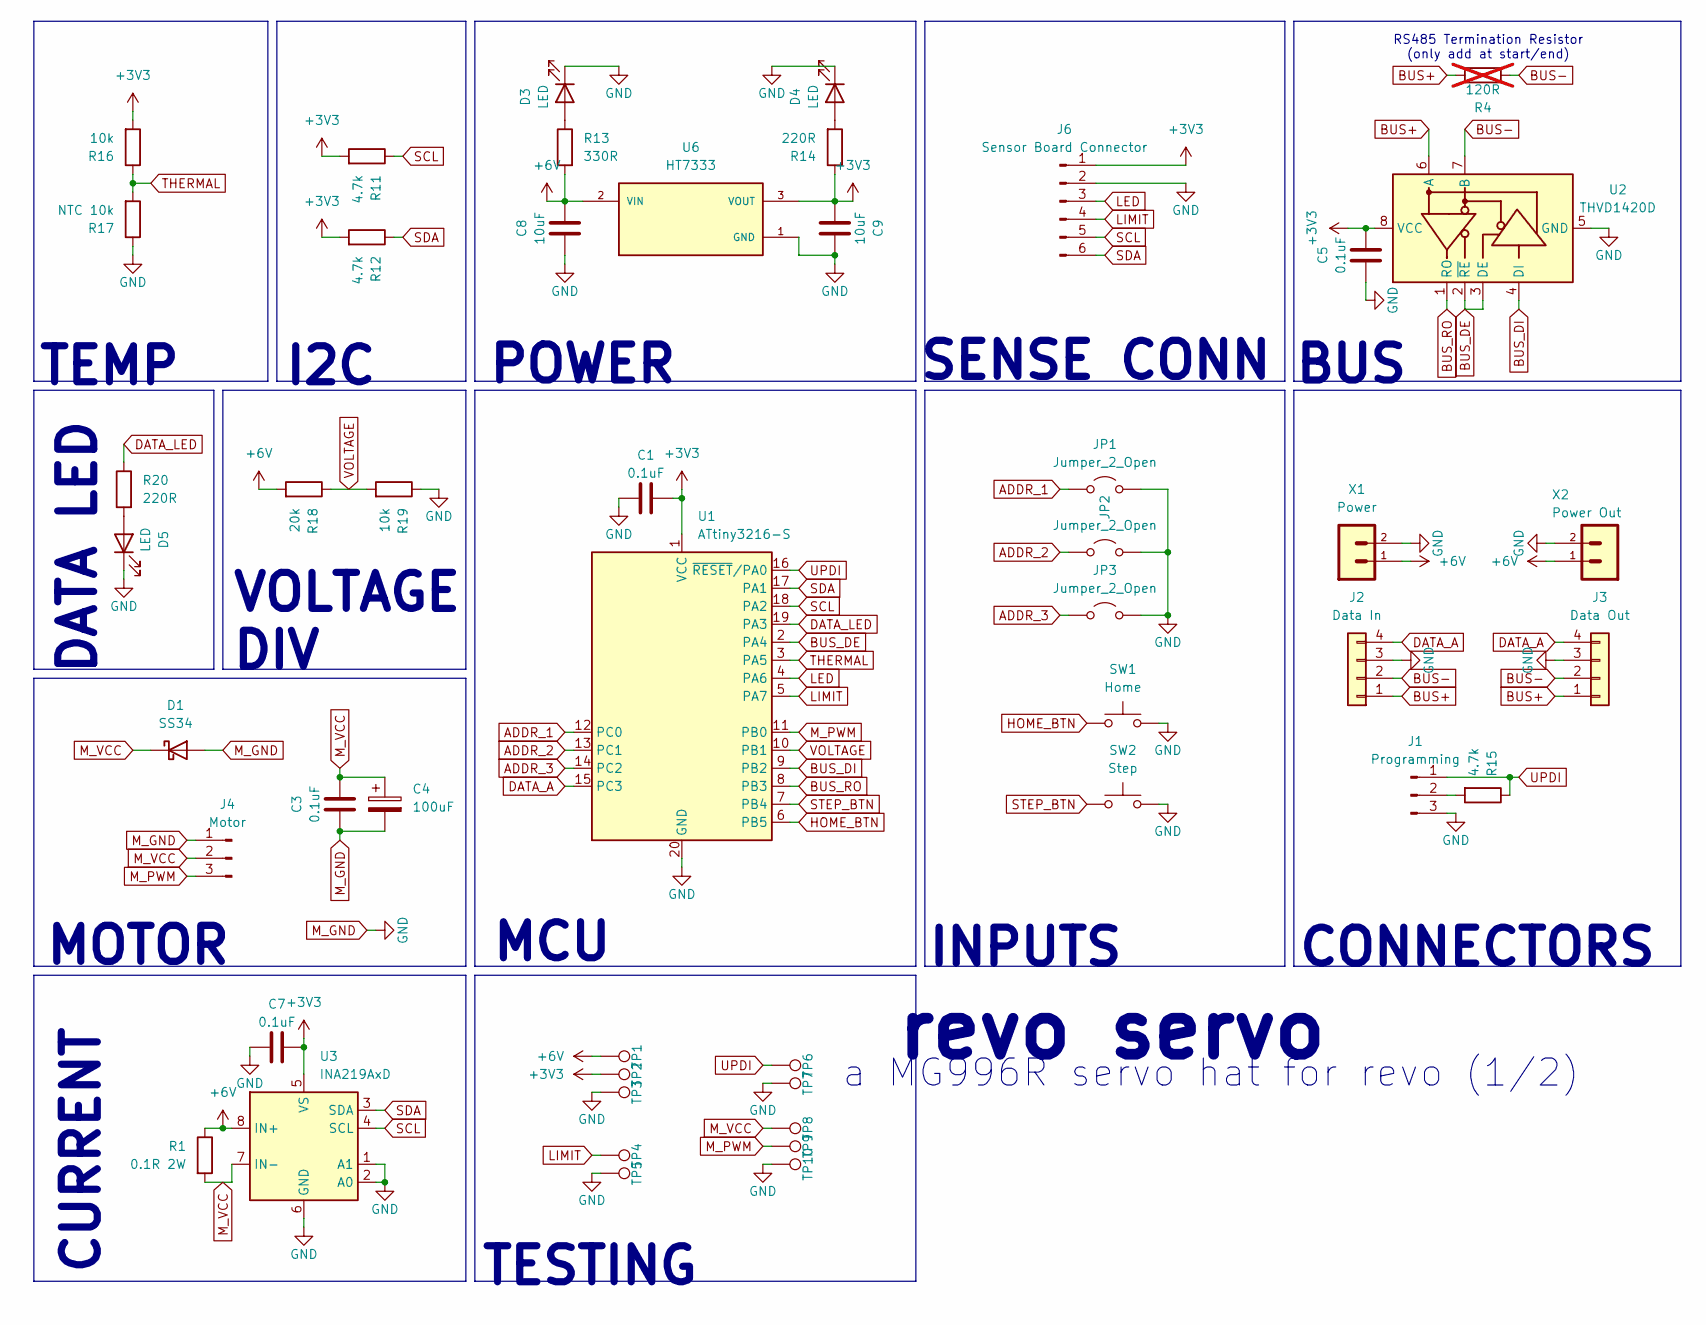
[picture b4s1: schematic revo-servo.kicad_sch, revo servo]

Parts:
C1, C3, C5, C7: 0.1uF; C_0805_2012Metric_Pad1.18x1.45mm_HandSolder
C4: 100uF; CP_Elec_6.3x5.4
C8, C9: 10uF; C_0805_2012Metric_Pad1.18x1.45mm_HandSolder
D1: SS34; D_SMA
D3, D4, D5: LED; D_0805_2012Metric_Pad1.15x1.40mm_HandSolder
J1: Programming; PinSocket_1x03_P2.54mm_Vertical
J2: Data In; JST_1x04_P1.25mm_Locking_Horizontal_SMD
J3: Data Out; JST_1x04_P1.25mm_Locking_Horizontal_SMD
J4: Motor; PinSocket_1x03_P2.54mm_Vertical
J6: Sensor Board Connector; PinHeader_1x06_P2.54mm_Horizontal
JP1, JP2, JP3: Jumper_2_Open; SolderJumper-2_P1.3mm_Open_TrianglePad1.0x1.5mm
R1: 0.1R 2W; R_2512_6332Metric_Pad1.40x3.35mm_HandSolder
R4: 120R; R_0805_2012Metric_Pad1.20x1.40mm_HandSolder; not fitted
R11, R12, R15: 4.7k; R_0805_2012Metric_Pad1.20x1.40mm_HandSolder
R13: 330R; R_0805_2012Metric_Pad1.20x1.40mm_HandSolder
R14, R20: 220R; R_0805_2012Metric_Pad1.20x1.40mm_HandSolder
R16, R19: 10k; R_0805_2012Metric_Pad1.20x1.40mm_HandSolder
R17: NTC 10k; R_Axial_DIN0204_L3.6mm_D1.6mm_P5.08mm_Horizontal
R18: 20k; R_0805_2012Metric_Pad1.20x1.40mm_HandSolder
SW1: Home; SW_Tactile_SPST_NO_Straight_CK_PTS636Sx25SMTRLFS
SW2: Step; SW_Tactile_SPST_NO_Straight_CK_PTS636Sx25SMTRLFS
TP1, TP2, TP3, TP4, TP5, TP6, TP7, TP8, TP9, TP10: 1.0mm; TestPoint-1.0mm
U1: ATtiny3216-S; SOIC-20W_7.5x12.8mm_P1.27mm
U2: THVD1420D; SOIC-8_3.9x4.9mm_P1.27mm
U3: INA219AxD; SOIC-8_3.9x4.9mm_P1.27mm
U6: HT7333; IC_HT7333; PARTREV 1.80
X1: Power; B2PS-VH
X2: Power Out; B2PS-VH

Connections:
+3V3: C1.2, C5.2, C7.2, C9.2, J6.1, R11.2, R12.2, R14.1, R16.2, TP2.1 (1_1), U1.1 (VCC), U2.8 (VCC), U3.5 (VS), U6.3 (VOUT)
+6V: C8.2, R1.1, R13.2, R18.2, TP1.1 (1_1), U3.8 (IN+), U6.2 (VIN), X1.1, X2.1
ADDR_1: JP1.1 (A), U1.12 (PC0)
ADDR_2: JP2.1 (A), U1.13 (PC1)
ADDR_3: JP3.1 (A), U1.14 (PC2)
BUS+: J2.1, J3.1, R4.1, U2.6 (A)
BUS-: J2.2, J3.2, R4.2, U2.7 (B)
BUS_DE: U1.2 (PA4), U2.2 (~RE), U2.3 (DE)
BUS_DI: U1.9 (PB2), U2.4 (DI)
BUS_RO: U1.8 (PB3), U2.1 (RO)
DATA_A: J2.4, J3.4, U1.15 (PC3)
DATA_LED: R20.1, U1.19 (PA3)
HOME_BTN: SW1.1, U1.6 (PB5)
LED: J6.3, U1.4 (PA6)
LIMIT: J6.4, TP4.1 (1_1), U1.5 (PA7)
M_GND: C1.1, C3.1, C4.2, C5.1, C7.1, C8.1, C9.1, D1.2 (A), D3.1 (K), D4.1 (K), D5.1 (K), J1.3, J2.3, J3.3, J4.1, J6.2, JP1.2 (B), JP2.2 (B), JP3.2 (B), R17.1, R19.1, SW1.2, SW2.2, TP3.1 (1_1), TP5.1 (1_1), TP7.1 (1_1), TP10.1 (1_1), U1.20 (GND), U2.5 (GND), U3.1 (A1), U3.2 (A0), U3.6 (GND), U6.1 (GND), X1.2, X2.2
M_PWM: J4.3, TP9.1 (1_1), U1.11 (PB0)
M_VCC: C3.2, C4.1, D1.1 (K), J4.2, R1.2, TP8.1 (1_1), U3.7 (IN-)
unnamed: D3.2 (A), R13.1
unnamed: D4.2 (A), R14.2
unnamed: D5.2 (A), R20.2
unnamed: J1.2, R15.2
SCL: J6.5, R11.1, U1.18 (PA2), U3.4 (SCL)
SDA: J6.6, R12.1, U1.17 (PA1), U3.3 (SDA)
STEP_BTN: SW2.1, U1.7 (PB4)
THERMAL: R16.1, R17.2, U1.3 (PA5)
UPDI: J1.1, R15.1, TP6.1 (1_1), U1.16 (~RESET/PA0)
VOLTAGE: R18.1, R19.2, U1.10 (PB1)

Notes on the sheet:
INPUTS
MCU
MOTOR
SENSE CONN
CURRENT
TEMP
RS485 Termination Resistor (only add at start/end)
I2C
revo servo
a MG996R servo hat for revo (1/2)
POWER
BUS
TESTING
DATA LED
VOLTAGE DIV
CONNECTORS
